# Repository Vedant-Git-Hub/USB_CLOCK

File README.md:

# USB_CLOCK
This repo consist of PCB, schematics and software for the USB clock hardwrae.

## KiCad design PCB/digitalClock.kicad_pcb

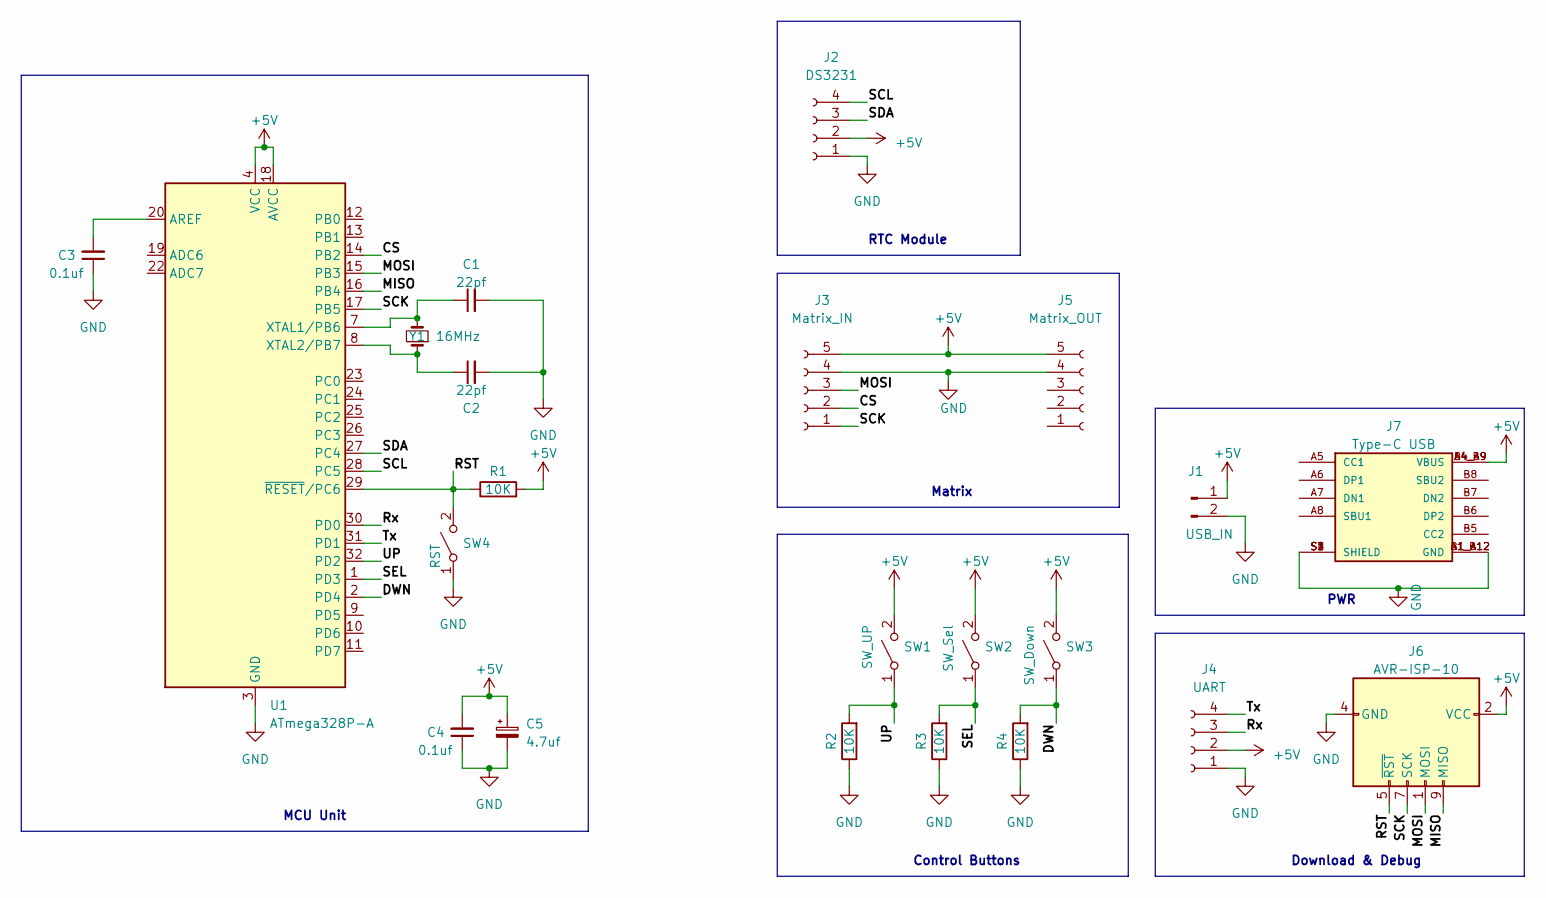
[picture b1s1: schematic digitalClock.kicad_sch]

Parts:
C1, C2: 22pf; C_1206_3216Metric_Pad1.33x1.80mm_HandSolder
C3, C4: 0.1uf; C_1206_3216Metric_Pad1.33x1.80mm_HandSolder
C5: 4.7uf; CP_Radial_D5.0mm_P2.50mm
J1: USB_IN; PinHeader_1x02_P2.54mm_Vertical
J2: DS3231; PinHeader_1x04_P2.54mm_Vertical
J3: Matrix_IN; PinHeader_1x05_P2.54mm_Vertical
J4: UART; PinHeader_1x04_P2.54mm_Vertical
J5: Matrix_OUT; PinHeader_1x05_P2.54mm_Vertical
J6: AVR-ISP-10; PinHeader_2x05_P2.54mm_Vertical
J7: Type-C USB; TYPE-C USB Female; PARTREV B
R1, R2, R3, R4: 10K; R_1206_3216Metric_Pad1.30x1.75mm_HandSolder
SW1: SW_UP; SW_PUSH_6mm
SW2: SW_Sel; SW_PUSH_6mm
SW3: SW_Down; SW_PUSH_6mm
SW4: RST; SW_Push_1P1T_XKB_TS-1187A
U1: ATmega328P-A; TQFP-32_7x7mm_P0.8mm
Y1: 16MHz; Crystal_HC52-6mm_Vertical

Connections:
+5V: C4.2, C5.1, J1.1, J2.2, J3.5, J4.2, J5.5, J6.2 (VCC), J7.A4_B9 (VBUS), J7.B4_A9 (VBUS), R1.2, SW1.2 (B), SW2.2 (B), SW3.2 (B), U1.4 (VCC), U1.6 (VCC), U1.18 (AVCC)
/CS: J3.2, U1.14 (PB2)
/DWN: R4.2, SW3.1 (A), U1.2 (PD4)
/MISO: J6.9 (MISO), U1.16 (PB4)
/MOSI: J3.3, J6.1 (MOSI), U1.15 (PB3)
/RST: J6.5 (~RST), R1.1, SW4.2 (B), U1.29 (~RESET/PC6)
/Rx: J4.3, U1.30 (PD0)
/SCK: J3.1, J6.7 (SCK), U1.17 (PB5)
/SCL: J2.4, U1.28 (PC5)
/SDA: J2.3, U1.27 (PC4)
/SEL: R3.2, SW2.1 (A), U1.1 (PD3)
/Tx: J4.4, U1.31 (PD1)
/UP: R2.2, SW1.1 (A), U1.32 (PD2)
GND: C1.2, C2.2, C3.1, C4.1, C5.2, J1.2, J2.1, J3.4, J4.1, J5.4, J6.4 (GND), J6.6 (GND), J6.8 (GND), J6.10 (GND), J7.A1_B12 (GND), J7.B1_A12 (GND), J7.S1 (SHIELD), J7.S2 (SHIELD), J7.S3 (SHIELD), J7.S4 (SHIELD), R2.1, R3.1, R4.1, SW4.1 (A), U1.3 (GND), U1.5 (GND), U1.21 (GND)
unnamed: C3.2, U1.20 (AREF)
unnamed: C1.1, U1.7 (XTAL1/PB6), Y1.2
unnamed: C2.1, U1.8 (XTAL2/PB7), Y1.1

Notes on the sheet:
Control Buttons
Matrix
MCU Unit
RTC Module
PWR
Download & Debug

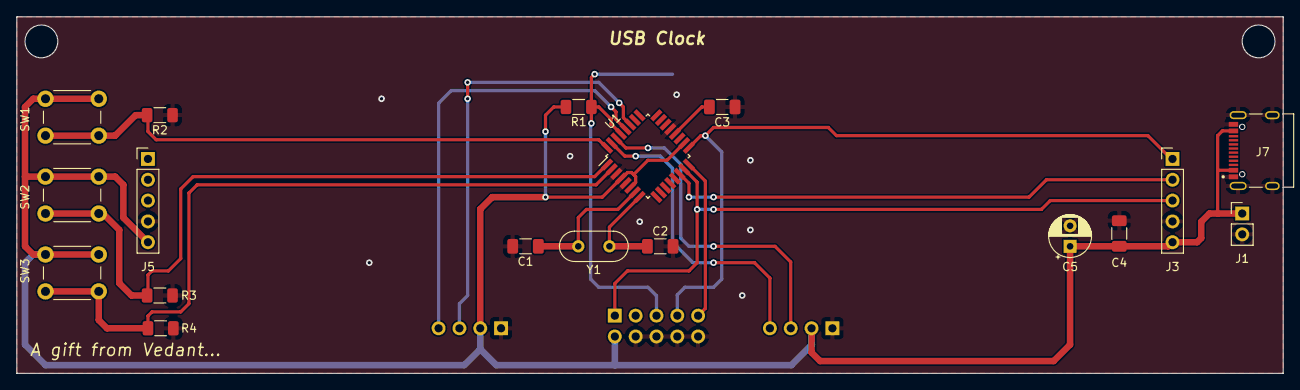
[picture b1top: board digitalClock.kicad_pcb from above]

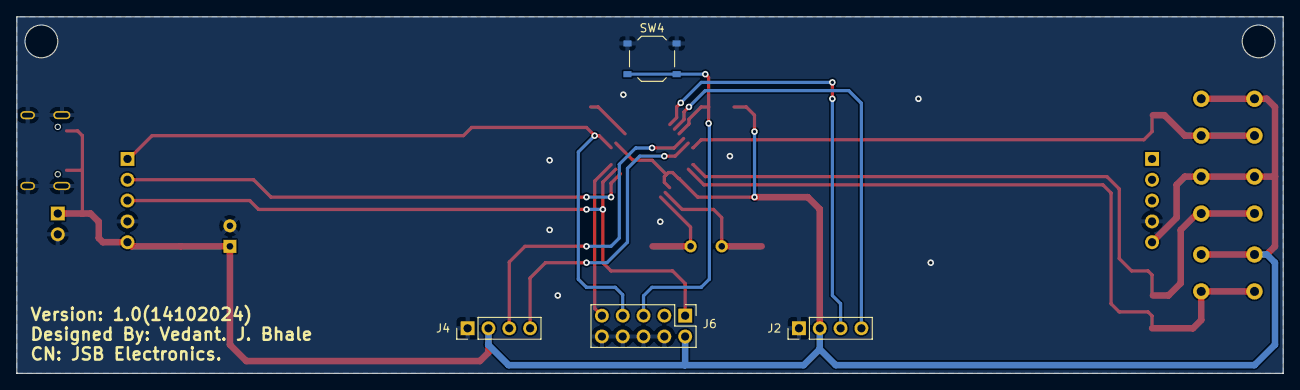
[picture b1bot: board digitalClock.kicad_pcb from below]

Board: 2 copper layers, 154.5 x 43.5 mm, 22 parts (4 on the bottom side), 17 nets.

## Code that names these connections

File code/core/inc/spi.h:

#ifndef H_SPI_H
#define H_SPI_H

#include <stdint.h>

#define MOSI_DIR        PB3
#define MISO_DIR        PB4
#define SCK_DIR         PB5
#define CS              PB2
 
 
void spi_init(void);
void spi_writeByte(uint8_t );
void spi_setCS(void);
void spi_resetCS(void);
void spi_transmitBytes(uint8_t *, uint8_t );

#endif

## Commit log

2026-05-22 First commit, added existing code base to github.
2026-05-22 Added time and date setting functionality via menu.
2026-05-22 Updated scroll text function to check if there are any valid button inputs present, if present it will terminate the current on going scroll and move to the action item for the pressed button.
2026-05-22 Added default states for dow and date.
2026-05-22 Fixed scrolling issue when button pressed.
2026-05-22 Removed useless states from menu.
2026-05-22 Added brightness feature to the clock via menu.
2026-05-22 Added temperature reading API to ds3231 driver and added temperature to menu.
2026-05-22 Adjusted temperature display start pixel.
